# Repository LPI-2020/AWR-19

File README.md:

# Analog Waiter Robot (AWR-19)

Developed in:
- Projeto Integrador - LPI I (2020)

Members:
- Bruno Miguel Vasconcelos da Silva, a88289
- Diogo Miguel Cunha Fernandes, a88262
- Duarte Miguel Novo Rodrigues, a88259
- Francisco Lopes Salgado, a88231 
- João Pedro Dias Miranda, a88237
- José Tomás Lima de Abreu, a88218

Directed by:
- Luís Barros

Short description (PT):
- O Analog Waiter Robot (AWR) é um robô seguidor de linha focado na assistência a pessoas em isolamento que não podem contactar com o mundo exterior. Basta colocar no seu suporte o que pretende fazer chegar ao paciente, colocá-lo sobre a linha, ligá-lo e este seguirá o percurso até ao destino.

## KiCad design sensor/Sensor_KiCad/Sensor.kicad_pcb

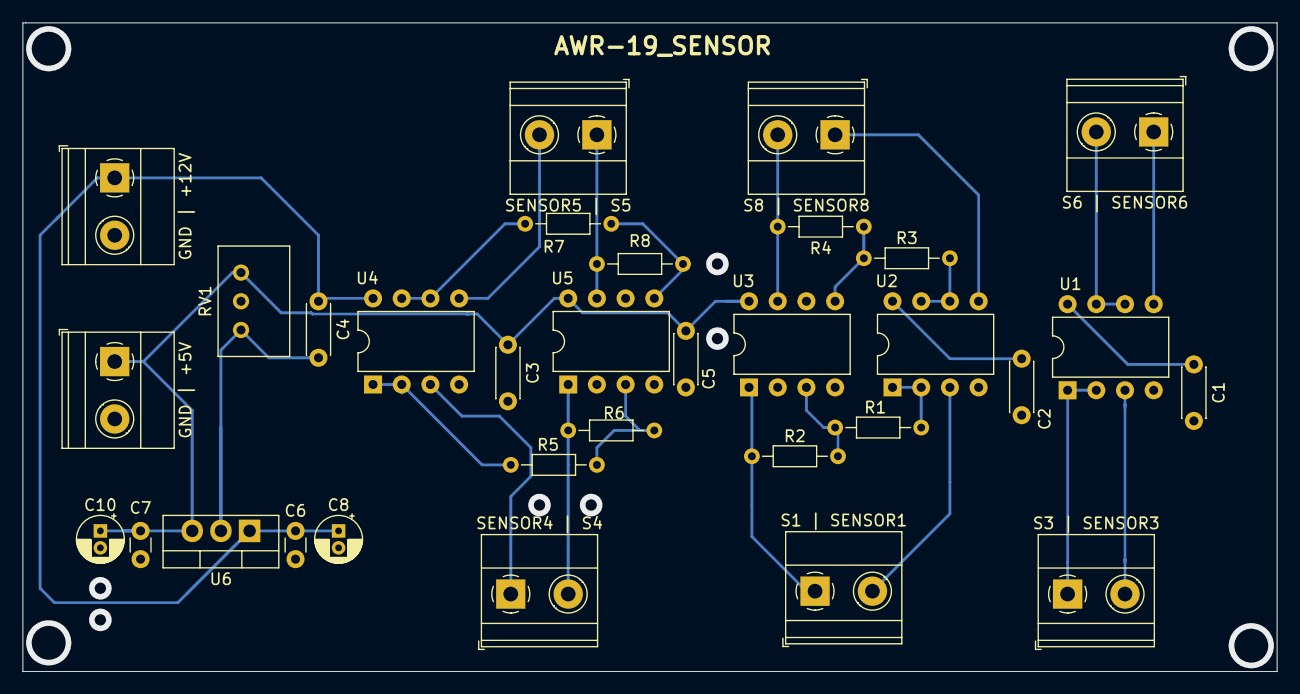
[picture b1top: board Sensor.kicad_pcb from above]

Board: 2 copper layers, 111.0 x 57.4 mm, 32 parts (0 on the bottom side), 24 nets.

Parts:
C1, C2, C3, C4, C5: C; C_Disc_D4.3mm_W1.9mm_P5.00mm
C6, C7: C; C_Disc_D3.0mm_W1.6mm_P2.50mm
C8, C10: CP_Small; CP_Radial_D4.0mm_P1.50mm
GND | +5V, GND | +12V: Conn_01x02_Female; TerminalBlock_Phoenix_MKDS-1,5-2-5.08_1x02_P5.08mm_Horizont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
R1, R3: 1k; R_Axial_DIN0204_L3.6mm_D1.6mm_P7.62mm_Horizontal
R2, R4: 10k; R_Axial_DIN0204_L3.6mm_D1.6mm_P7.62mm_Horizontal
R5, R6, R7, R8: R; R_Axial_DIN0204_L3.6mm_D1.6mm_P7.62mm_Horizontal
RV1: R_POT; Potentiometer_Bourns_3299W_Vertical
S1 | SENSOR1, S3 | SENSOR3, S6 | SENSOR6, S8 | SENSOR8: Conn_01x02_Female; TerminalBlock_Phoenix_MKDS-1,5-2-5.08_1x02_P5.08mm_Horizont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
SENSOR4 | S4, SENSOR5 | S5: Conn_01x02_Female; TerminalBlock_Phoenix_MKDS-1,5-2-5.08_1x02_P5.08mm_Horizont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
U1, U2, U3, U4, U5: LM358; DIP-8_W7.62mm
U6: LM7805_TO220; TO-220-3_Vertical

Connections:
+5V: C3.1, C5.1, C7.1, C10.1, GND | +5V.1, RV1.1, U3.8, U5.8, U6.3
+12V: C1.1, C2.1, C4.1, C6.1, C8.1, GND | +12V.1, U1.8, U2.8, U4.8, U6.1
GND: C1.2, C2.2, C3.2, C4.2, C5.2, C6.2, C7.2, C8.2, C10.2, GND | +5V.2, GND | +12V.2, RV1.3, U1.4, U2.4, U3.4, U4.4, U5.4, U6.2
IN_SENSOR1: S1 | SENSOR1.2, U2.3
IN_SENSOR3: S3 | SENSOR3.2, U1.3
IN_SENSOR4: SENSOR4 | S4.1, U4.3
IN_SENSOR5: SENSOR5 | S5.2, U4.5
IN_SENSOR6: S6 | SENSOR6.1, U1.5
IN_SENSOR8: S8 | SENSOR8.1, U2.5
unnamed: R1.1, U2.1, U2.2
unnamed: R1.2, R2.1, U3.3
unnamed: R3.1, U2.6, U2.7
unnamed: R3.2, R4.1, U3.5
unnamed: R5.1, U4.1, U4.2
unnamed: R5.2, R6.1, U5.3
unnamed: R7.1, U4.6, U4.7
unnamed: R7.2, R8.1, U5.5
OUT_SENSOR1: R2.2, S1 | SENSOR1.1, U3.1
OUT_SENSOR3: S3 | SENSOR3.1, U1.1, U1.2
OUT_SENSOR4: R6.2, SENSOR4 | S4.2, U5.1
OUT_SENSOR5: R8.2, SENSOR5 | S5.1, U5.7
OUT_SENSOR6: S6 | SENSOR6.2, U1.6, U1.7
OUT_SENSOR8: R4.2, S8 | SENSOR8.2, U3.7
VREF: RV1.2, U3.2, U3.6, U5.2, U5.6

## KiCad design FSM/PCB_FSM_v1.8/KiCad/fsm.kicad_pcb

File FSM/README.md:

# PI-LPI_I/FSM

**_Version_ currently in use: v1.8**

Resources - Holds various materials that helped or will help implement features.

v1 - Robot makes 180 degree turn when arriving at the end of the line and then stops.
     After that, whenever the user wants to send back the robot, a button can be pressed to begin movement.

v2 - Robot stops at the end of the line. After that, whenever the user wants to send back the robot,
     a button can be pressed to begin movement in the opposite direction that he came.

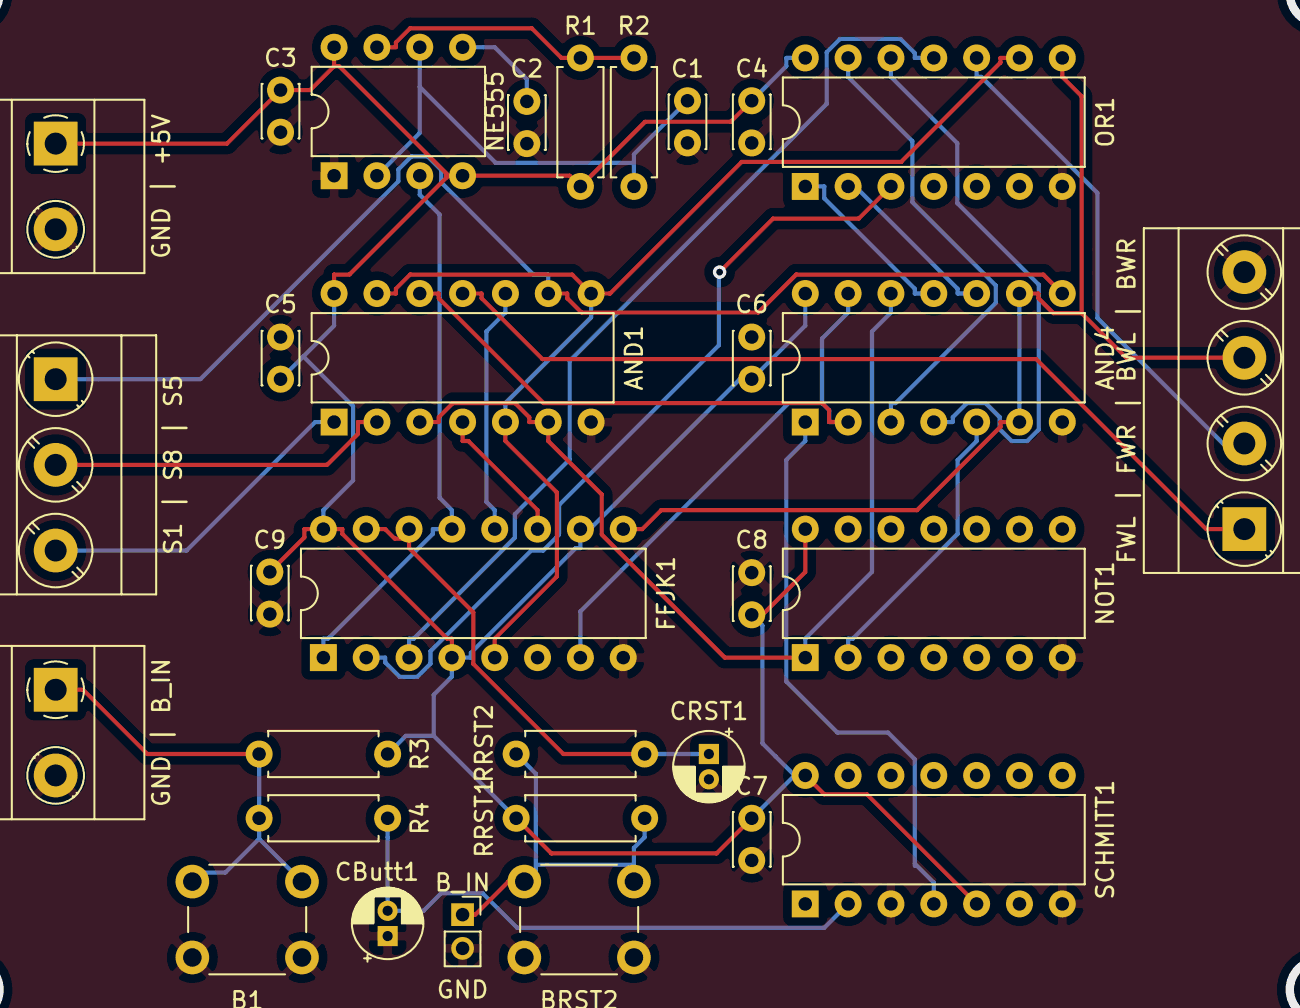
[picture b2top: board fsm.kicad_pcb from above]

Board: 2 copper layers, 31 parts (0 on the bottom side), 29 nets.

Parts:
AND1, AND4: 4081; DIP-14_W7.62mm
B1: SW_Push; SW_PUSH_6mm_H7.3mm
BRST2: SW_Push; SW_PUSH_6mm_H7.3mm
C1: 4,7u; C_Disc_D3.0mm_W2.0mm_P2.50mm
C2, C3, C4, C5, C6, C7, C8, C9: 10n; C_Disc_D3.0mm_W2.0mm_P2.50mm
CButt1: 10n; CP_Radial_D4.0mm_P1.50mm
CRST1: 10n; CP_Radial_D4.0mm_P1.50mm
FFJK1: 74LS76; DIP-16_W7.62mm
FWL | FWR | BWL | BWR: Conn_01x04_Female; TerminalBlock_Phoenix_MKDS-3-4-5.08_1x04_P5.08mm_Horizontal
GND: Conn_01x02_Female; PinSocket_1x02_P2.00mm_Vertical
GND | +5V: Conn_01x02_Female; TerminalBlock_Phoenix_MKDS-1,5-2-5.08_1x02_P5.08mm_Horizont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
GND | B_IN: Conn_01x02_Female; TerminalBlock_Phoenix_MKDS-1,5-2-5.08_1x02_P5.08mm_Horizont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
NE555: NE555P; DIP-8_W7.62mm
NOT1: 74LS04; DIP-14_W7.62mm
OR1: 4071; DIP-14_W7.62mm
R1: 6,2k; R_Axial_DIN0207_L6.3mm_D2.5mm_P7.62mm_Horizontal
R2: 150k; R_Axial_DIN0207_L6.3mm_D2.5mm_P7.62mm_Horizontal
R3: 10k; R_Axial_DIN0207_L6.3mm_D2.5mm_P7.62mm_Horizontal
R4: 1k; R_Axial_DIN0207_L6.3mm_D2.5mm_P7.62mm_Horizontal
RRST1, RRST2: 100k; R_Axial_DIN0207_L6.3mm_D2.5mm_P7.62mm_Horizontal
S1 | S8 | S5: Conn_01x03_Female; TerminalBlock_Phoenix_MKDS-3-3-5.08_1x03_P5.08mm_Horizontal
SCHMITT1: SN74LVC1G14DRL; DIP-14_W7.62mm

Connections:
+5V: AND1.14, AND4.14, C3.1, C4.1, C5.1, C6.1, C7.1, C8.1, C9.1, FFJK1.4, FFJK1.10, FFJK1.16, GND | +5V.1, NE555.4, NE555.8, NOT1.14, OR1.14, R1.1, R3.1, RRST1.1, SCHMITT1.5, SCHMITT1.14
B: AND4.1, SCHMITT1.4
B0: AND1.5, AND1.8, AND1.13, FFJK1.5, OR1.9
B1': AND1.12, AND4.2, AND4.13, FFJK1.7
BWL: AND4.6, AND4.9, FFJK1.9, FWL | FWR | BWL | BWR.3, OR1.8
B_IN: B1.2, GND | B_IN.1, R3.2, R4.1
CLK: FFJK1.1, FFJK1.13, NE555.3
FWL: AND1.11, FWL | FWR | BWL | BWR.1
FWR: FWL | FWR | BWL | BWR.2, OR1.10
GND: AND1.7, AND4.7, B1.1, BRST2.1, C1.2, C2.1, C3.2, C4.2, C5.2, C6.2, C7.2, C8.2, C9.2, CButt1.1, CRST1.2, FFJK1.8, FWL | FWR | BWL | BWR.4, GND.2, GND | +5V.2, GND | B_IN.2, NE555.1, NOT1.7, OR1.7, SCHMITT1.3, SCHMITT1.7
unnamed: AND1.3, AND1.6, AND4.12, NOT1.1
unnamed: AND1.4, FFJK1.11
unnamed: AND1.10, FFJK1.12
unnamed: AND4.3, OR1.13
unnamed: AND4.4, OR1.12
unnamed: AND4.5, NOT1.2
unnamed: AND4.10, OR1.2
unnamed: AND4.11, OR1.1
unnamed: BRST2.2, GND.1, RRST1.2, RRST2.1
unnamed: C1.1, NE555.2, NE555.6, R2.2
unnamed: C2.2, NE555.5
unnamed: CButt1.2, R4.2, SCHMITT1.2
unnamed: FFJK1.2, OR1.3
unnamed: FFJK1.3, OR1.11
unnamed: NE555.7, R1.2, R2.1
RESET: CRST1.1, FFJK1.14, FFJK1.15, RRST2.2
S1: AND1.1, S1 | S8 | S5.3
S5: AND1.9, AND4.8, S1 | S8 | S5.1
S8: AND1.2, S1 | S8 | S5.2

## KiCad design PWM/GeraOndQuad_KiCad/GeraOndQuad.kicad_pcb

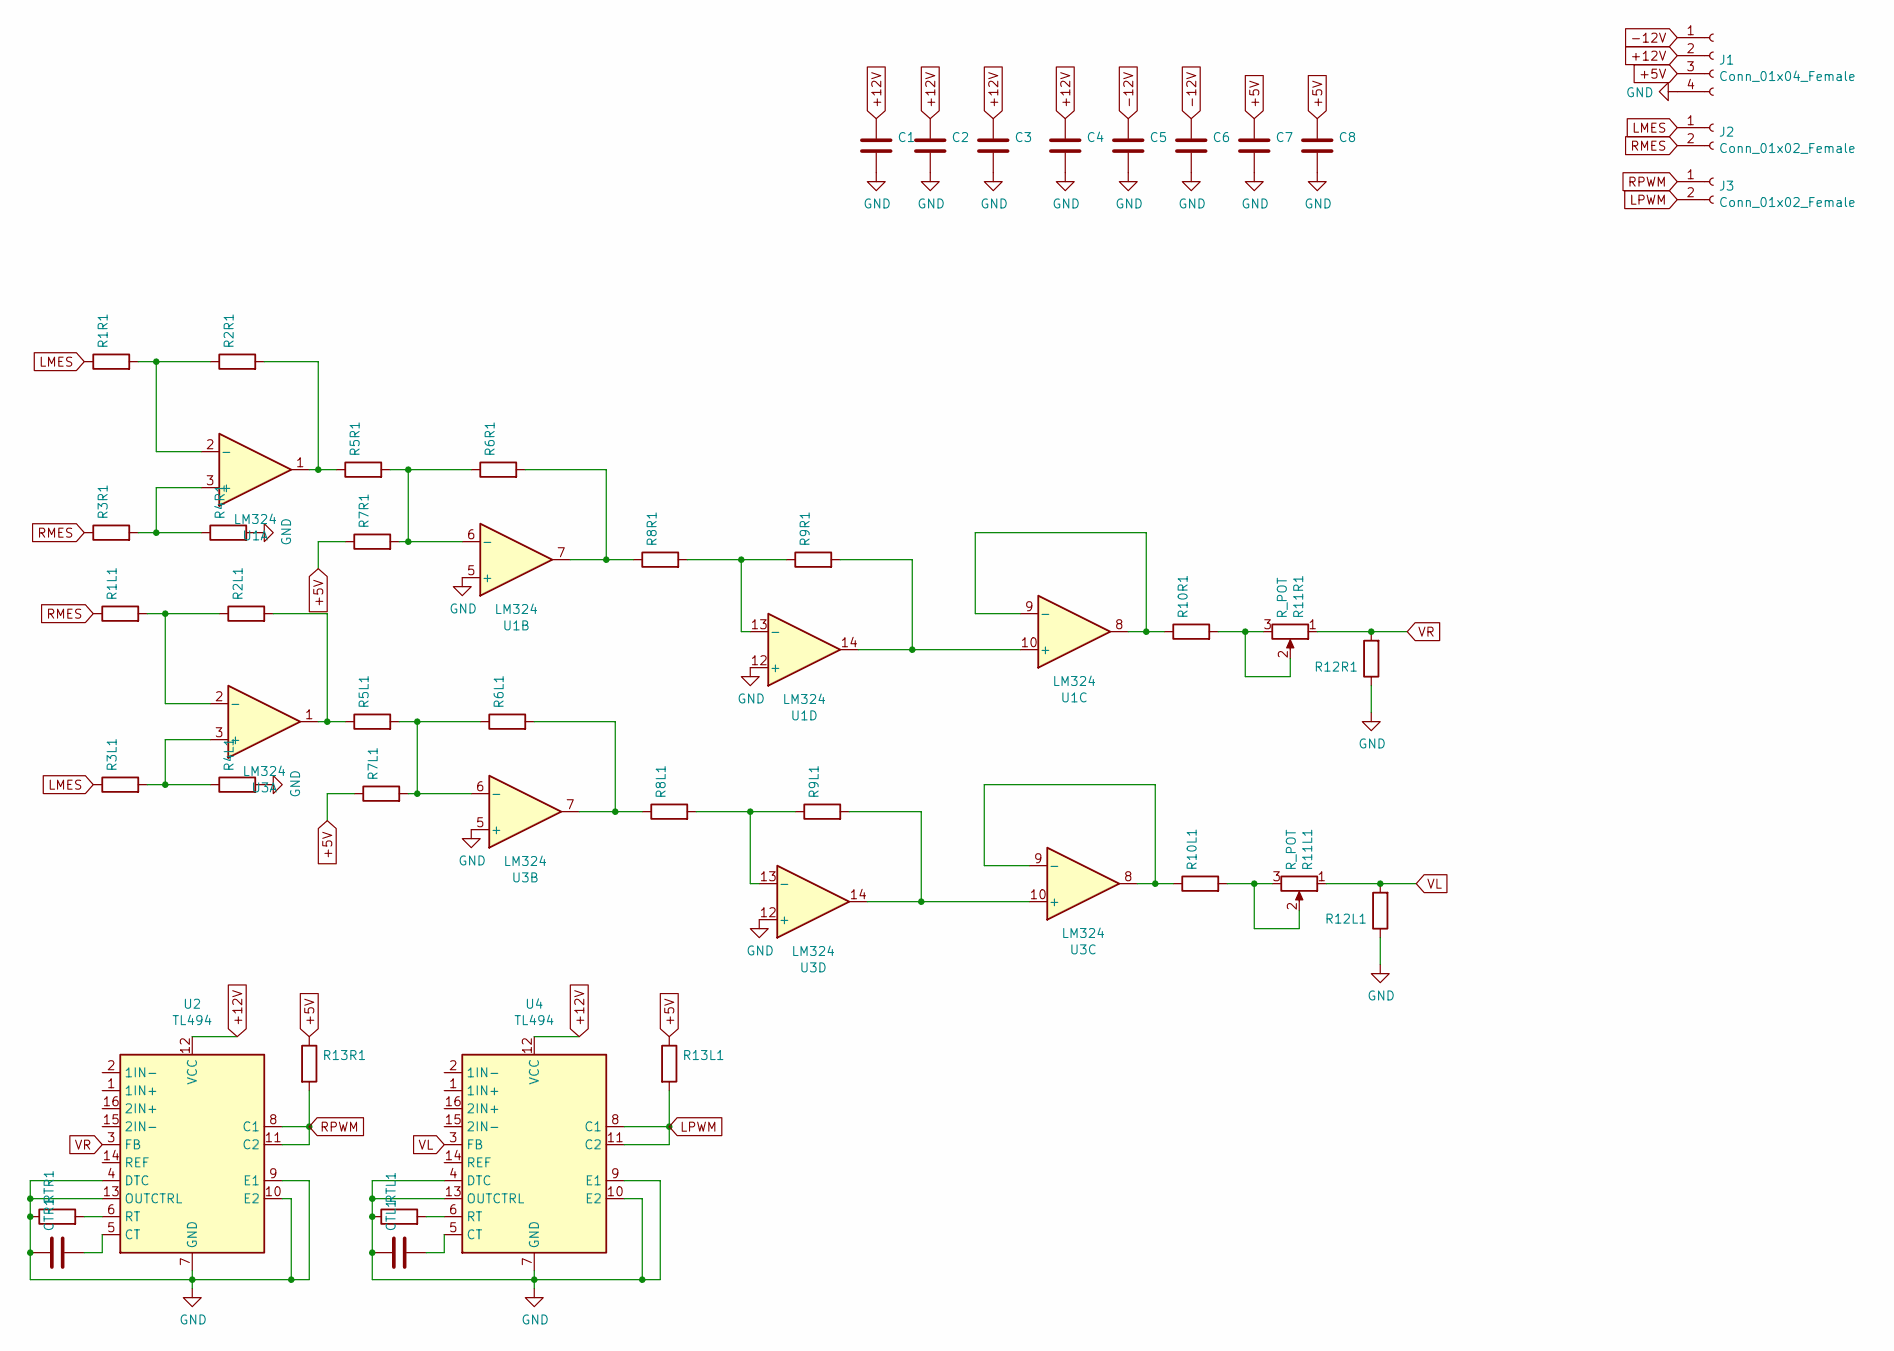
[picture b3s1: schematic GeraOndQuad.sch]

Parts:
C1, C2, C3, C4, C5, C6, C7, C8: C; C_Disc_D3.0mm_W1.6mm_P2.50mm
CTL1: C; C_Disc_D3.0mm_W1.6mm_P2.50mm
CTR1: C; C_Disc_D3.0mm_W1.6mm_P2.50mm
J1: Conn_01x04_Female; TerminalBlock_Phoenix_MKDS-1,5-4_1x04_P5.00mm_Horizontal
J2, J3: Conn_01x02_Female; TerminalBlock_Phoenix_MKDS-1,5-2-5.08_1x02_P5.08mm_Horizont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
R1L1, R1R1, R2L1, R2R1, R3L1, R3R1, R4L1, R4R1, R5L1, R5R1, R6L1, R6R1, R7L1, R7R1, R8L1, R8R1, R9L1, R9R1, R10L1, R10R1, R12L1, R12R1, R13L1, R13R1: R; R_Axial_DIN0204_L3.6mm_D1.6mm_P7.62mm_Horizontal
R11L1, R11R1: R_POT; Potentiometer_Bourns_3299W_Vertical
RTL1: R; R_Axial_DIN0204_L3.6mm_D1.6mm_P7.62mm_Horizontal
RTR1: R; R_Axial_DIN0204_L3.6mm_D1.6mm_P7.62mm_Horizontal
U1, U3: LM324; DIP-14_W7.62mm
U2, U4: TL494; DIP-16_W10.16mm

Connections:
+5V: C7.1, C8.1, J1.3, R7L1.1, R7R1.1, R13L1.1, R13R1.1; also elsewhere on the board
+12V: C1.1, C2.1, C3.1, C4.1, J1.2, U1.4 (V+), U2.12 (VCC), U3.4 (V+), U4.12 (VCC); also elsewhere on the board
-12V: C5.1, C6.1, J1.1, U1.11 (V-), U3.11 (V-); also elsewhere on the board
GND: C1.2, C2.2, C3.2, C4.2, C5.2, C6.2, C7.2, C8.2, CTL1.1, CTR1.1, J1.4, R4L1.2, R4R1.2, R12L1.1, R12R1.1, RTL1.1, RTR1.1, U1.5 (+), U1.12 (+), U2.4 (DTC), U2.7 (GND), U2.9 (E1), U2.10 (E2), U2.13 (OUTCTRL), U3.5 (+), U3.12 (+), U4.4 (DTC), U4.7 (GND), U4.9 (E1), U4.10 (E2), U4.13 (OUTCTRL); also elsewhere on the board
LMES: J2.1, R1R1.1, R3L1.1; also elsewhere on the board
LPWM: J3.2, R13L1.2, U4.8 (C1), U4.11 (C2); also elsewhere on the board
unnamed: CTL1.2, U4.5 (CT)
unnamed: CTR1.2, U2.5 (CT)
unnamed: R1L1.2, R2L1.1, U3.2 (-)
unnamed: R1R1.2, R2R1.1, U1.2 (-)
unnamed: R2L1.2, R5L1.1, U3.1
unnamed: R2R1.2, R5R1.1, U1.1
unnamed: R3L1.2, R4L1.1, U3.3 (+)
unnamed: R3R1.2, R4R1.1, U1.3 (+)
unnamed: R5L1.2, R6L1.1, R7L1.2, U3.6 (-)
unnamed: R5R1.2, R6R1.1, R7R1.2, U1.6 (-)
unnamed: R6L1.2, R8L1.1, U3.7
unnamed: R6R1.2, R8R1.1, U1.7
unnamed: R8L1.2, R9L1.1, U3.13 (-)
unnamed: R8R1.2, R9R1.1, U1.13 (-)
unnamed: R9L1.2, U3.10 (+), U3.14
unnamed: R9R1.2, U1.10 (+), U1.14
unnamed: R10L1.1, U3.8, U3.9 (-)
unnamed: R10L1.2, R11L1.2, R11L1.3
unnamed: R10R1.1, U1.8, U1.9 (-)
unnamed: R10R1.2, R11R1.2, R11R1.3
unnamed: RTL1.2, U4.6 (RT)
unnamed: RTR1.2, U2.6 (RT)
RMES: J2.2, R1L1.1, R3R1.1; also elsewhere on the board
RPWM: J3.1, R13R1.2, U2.8 (C1), U2.11 (C2); also elsewhere on the board
VL: R11L1.1, R12L1.2, U4.3 (FB)
VR: R11R1.1, R12R1.2, U2.3 (FB)

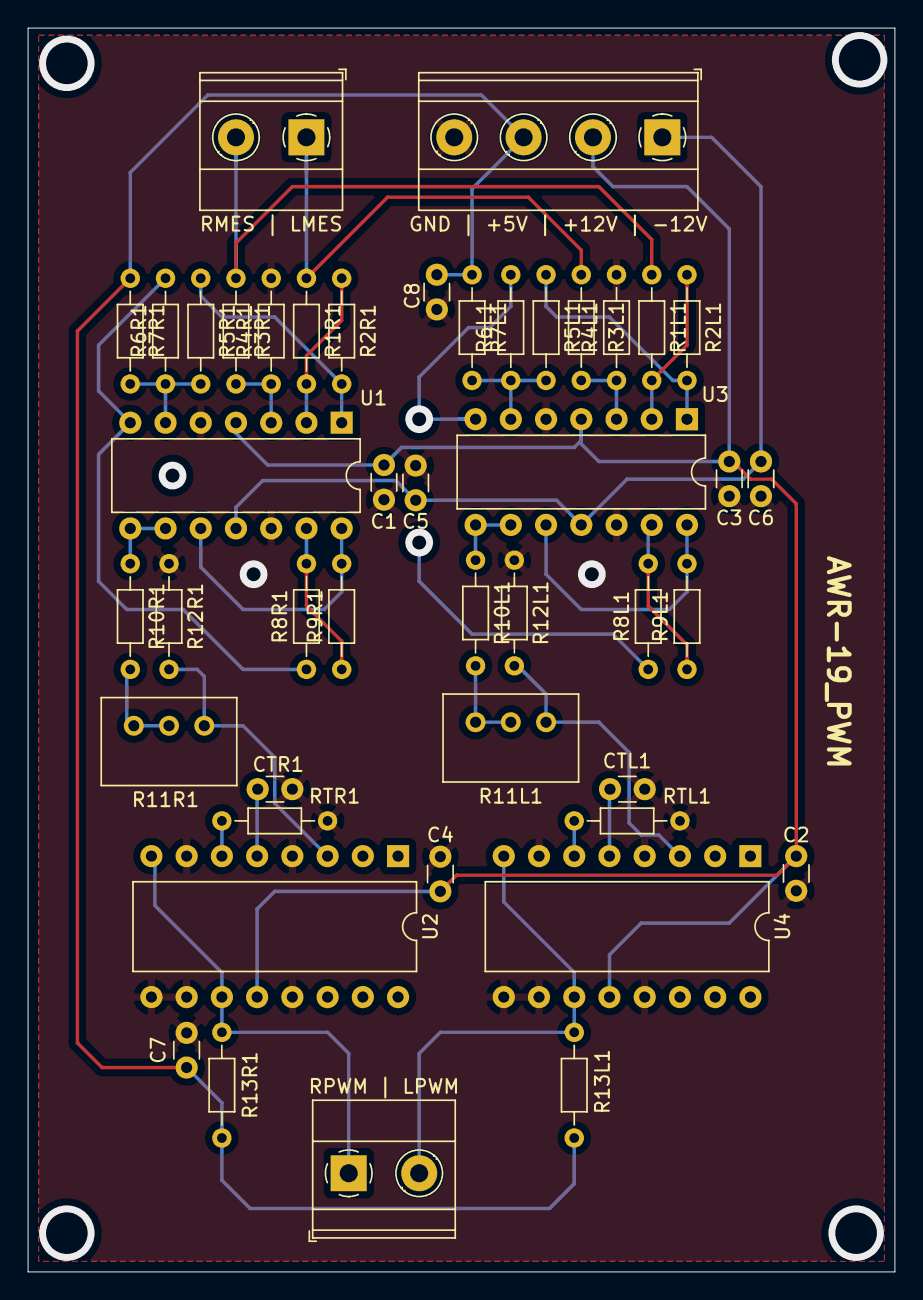
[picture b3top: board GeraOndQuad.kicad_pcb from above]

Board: 2 copper layers, 62.5 x 89.7 mm, 45 parts (0 on the bottom side), 32 nets.

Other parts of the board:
GND | +5V | +12V | -12V: Conn_01x04_Female; TerminalBlock_Phoenix_MKDS-1,5-4_1x04_P5.00mm_Horizontal
RMES | LMES: Conn_01x02_Female; TerminalBlock_Phoenix_MKDS-1,5-2-5.08_1x02_P5.08mm_Horizont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
RPWM | LPWM: Conn_01x02_Female; TerminalBlock_Phoenix_MKDS-1,5-2-5.08_1x02_P5.08mm_Horizont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

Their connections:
+5V: GND | +5V | +12V | -12V.3; also elsewhere on the board
+12V: GND | +5V | +12V | -12V.2; also elsewhere on the board
-12V: GND | +5V | +12V | -12V.1; also elsewhere on the board
GND: GND | +5V | +12V | -12V.4; also elsewhere on the board
LMES: RMES | LMES.1; also elsewhere on the board
LPWM: RPWM | LPWM.2; also elsewhere on the board
RMES: RMES | LMES.2; also elsewhere on the board
RPWM: RPWM | LPWM.1; also elsewhere on the board

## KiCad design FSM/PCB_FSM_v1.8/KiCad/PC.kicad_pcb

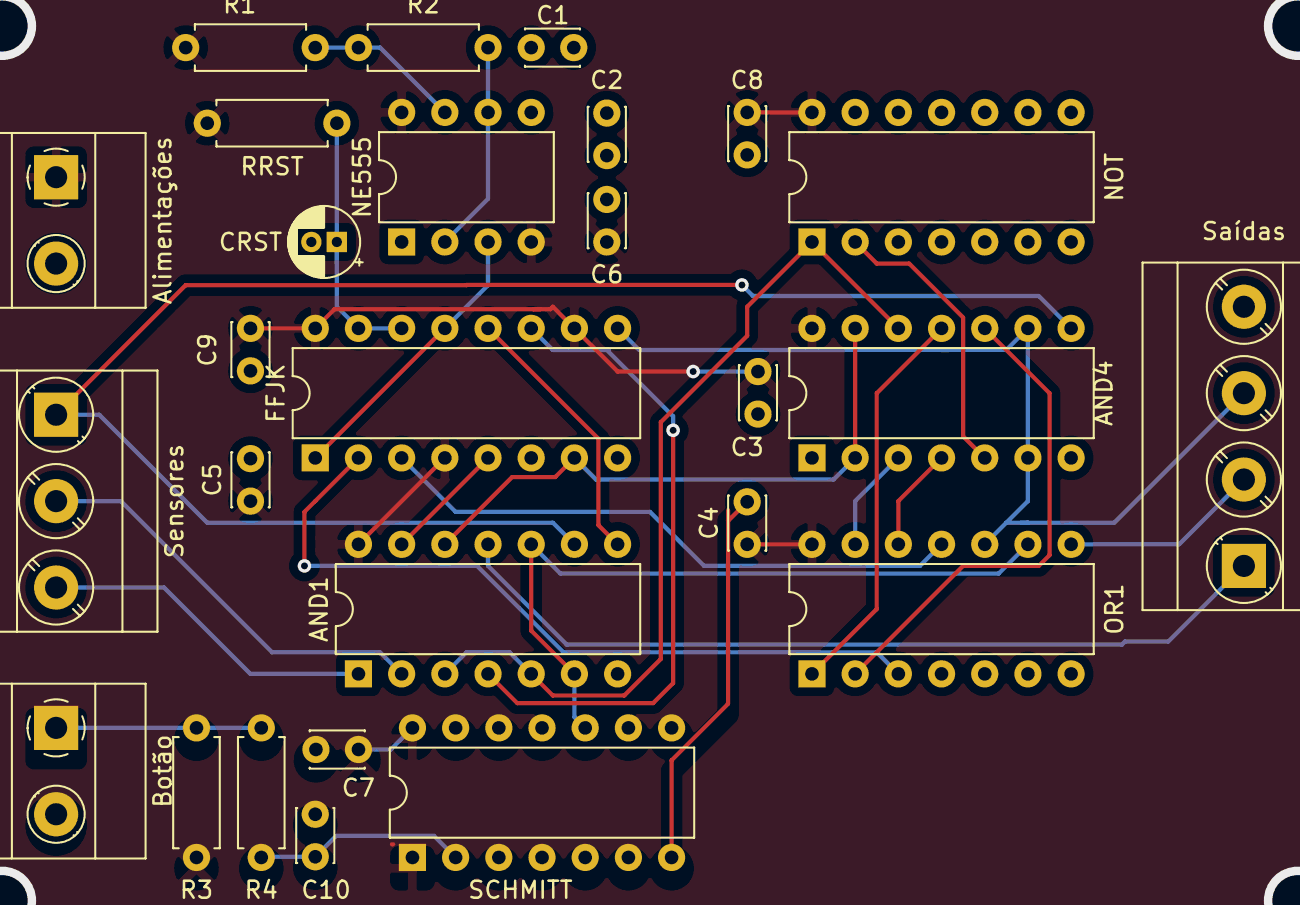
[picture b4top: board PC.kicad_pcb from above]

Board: 2 copper layers, 27 parts (0 on the bottom side), 27 nets.

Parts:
AND1, AND4: 4081; DIP-14_W7.62mm
Alimentações: Conn_01x02_Female; TerminalBlock_Phoenix_MKDS-1,5-2-5.08_1x02_P5.08mm_Horizont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
Botão: Conn_01x02_Female; TerminalBlock_Phoenix_MKDS-1,5-2-5.08_1x02_P5.08mm_Horizont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
C1: 4,7u; C_Disc_D3.0mm_W2.0mm_P2.50mm
C2, C3, C4, C5, C6, C7, C8, C9, C10: 10n; C_Disc_D3.0mm_W2.0mm_P2.50mm
CRST: 10n; CP_Radial_D4.0mm_P1.50mm
FFJK: 74LS76; DIP-16_W7.62mm
NE555: NE555P; DIP-8_W7.62mm
NOT: 74LS04; DIP-14_W7.62mm
OR1: 4071; DIP-14_W7.62mm
R1, R3, R4: 6,2k; R_Axial_DIN0207_L6.3mm_D2.5mm_P7.62mm_Horizontal
R2: 150k; R_Axial_DIN0207_L6.3mm_D2.5mm_P7.62mm_Horizontal
RRST: 100k; R_Axial_DIN0207_L6.3mm_D2.5mm_P7.62mm_Horizontal
SCHMITT: SN74LVC1G14DRL; DIP-14_W7.62mm
Saídas: Conn_01x04_Female; TerminalBlock_Phoenix_MKDS-3-4-5.08_1x04_P5.08mm_Horizontal
Sensores: Conn_01x03_Female; TerminalBlock_Phoenix_MKDS-3-3-5.08_1x03_P5.08mm_Horizontal

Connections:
+5V: AND1.14, AND4.14, Alimentações.1, C3.1, C4.1, C5.1, C6.1, C7.1, C8.1, C9.1, FFJK.4, FFJK.10, FFJK.16, NE555.4, NE555.8, NOT.14, OR1.14, R1.1, R3.1, RRST.1, SCHMITT.1, SCHMITT.14
B0: AND1.6, AND1.10, AND1.13, FFJK.5, OR1.9, SCHMITT.10
B1': AND1.12, AND4.2, AND4.13, FFJK.7
BWL: AND4.6, AND4.9, FFJK.9, OR1.10, Saídas.3
B_IN: Botão.1, R3.2, R4.1
CLK: FFJK.1, FFJK.13, NE555.3
FWL: AND1.11, Saídas.1
FWR: OR1.8, Saídas.2
GND: AND1.7, AND4.7, Alimentações.2, Botão.2, C1.2, C2.1, C3.2, C4.2, C5.2, C6.2, C7.2, C8.2, C9.2, C10.1, CRST.2, FFJK.8, NE555.1, NOT.7, OR1.7, SCHMITT.7, Saídas.4
unnamed: AND1.3, AND1.5, AND4.12, NOT.1
unnamed: AND1.4, FFJK.11
unnamed: AND1.8, FFJK.12
unnamed: AND4.3, OR1.13
unnamed: AND4.4, OR1.12
unnamed: AND4.5, NOT.2
unnamed: AND4.10, OR1.2
unnamed: AND4.11, OR1.1
unnamed: C1.1, NE555.2, NE555.6, R2.2
unnamed: C2.2, NE555.5
unnamed: C10.2, R4.2, SCHMITT.2
unnamed: FFJK.2, OR1.3
unnamed: FFJK.3, OR1.11
unnamed: NE555.7, R1.2, R2.1
RESET: CRST.1, FFJK.14, FFJK.15, RRST.2
S1: AND1.1, Sensores.3
S5: AND1.9, AND4.8, Sensores.1
S8: AND1.2, Sensores.2

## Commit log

2020-12-19 Added old updates.
2020-12-22 Added resources, updated ne555-simulations.
2020-12-22 Moved files from /fsm/resources to /documentation
2020-12-23 2.3 correction and 2.4
2020-12-24 add components and prices
2020-12-28 Removed non essential files
2020-12-29 Added templates for PADs projects.
2020-12-29 Added some notes - TODO.txt!
2020-12-30 Added push button pinout to /resources
2020-12-30 Added more notes to TODO.txt
2021-01-02 Adding some connections, in and out jumpers. Please, checkout TODO.txt.
2021-01-07 FSM/PCB_FSM/fsm_design_reduced is not working. Multisim bug i think
2021-01-20 Version 2.5 currently working
2021-01-20 Starting pcb_fsm
2021-01-21 Working on pcb_fsm
2021-01-23 PWM generator without a reference
2021-01-23 correction of some error
2021-01-23 sensor circuits
2021-01-24 add datasheet
2021-01-24 added excel with tests
2021-01-24 last version pads layout (with errors)
2021-01-24 continuation
2021-01-24 maybe it needs +12V on top
2021-01-25 Working on fsm_pcb
2021-01-25 PCB almost finished - no errors
2021-01-25 Added fsm_v1.8
2021-01-25 PCB v1.8
2021-01-25 PCB first changes
2021-01-25 sensor and pwm pcb finished
2021-01-25 holy shit
2021-01-25 added voltagegenerator
2021-01-25 added LM7805 datasheet
2021-01-26 Relatorio added
2021-01-26 Sensor PCB finished
2021-01-26 decoupling capacitors
2021-01-26 added voltage generator PCB
2021-01-26 FSM Relatorio Final
2021-01-26 minor errors corrected
2021-01-26 add voltageGenerator to PCB
2021-01-26 Relatório FSM
2021-01-26 PDF and DWG files for robot diagrams
2021-01-26 Fixed .sch errors
2021-01-26 Correct fsm diagram added
2021-01-27 GerOndQuad updated
2021-01-27 Sensor PCB corrected
2021-01-27 Struct
2021-01-27 Alterações no relatorio
2021-01-27 Relatório
2021-01-27 coadded comments in the simulation
2021-01-27 Sensor and GeraOndQuad finished
2021-01-27 PCB done
2021-01-27 Tina edited
2021-01-27 Added final fsm_pcb version
2021-01-27 Added tmp version of pcb_debounce
2021-01-27 Updated Mechanical Diagrams
    Almost complete, while viewing in pdf lines appear grey because they're too thin, this issue will get resolved later
2021-01-27 simulation edited
2021-01-27 iniciation
2021-01-27 Continuing Relatorio
2021-01-27 Added push-button logic & layout
2021-01-27 PTA Q PRREU
2021-01-28 Added fsm_LB
2021-01-28 added image
2021-01-28 bibliography
2021-01-28 added relatorio_revisao
2021-01-28 added Kickad sensor
2021-01-28 Added final version fsm_LB
2021-01-28 print simultions
2021-01-28 Diagram Updated and 3D Model Started
    Do not open the pdf file with Adobe Acrobat Reader to take prints, use other pdf viewer (chrome works for me) where lines don't appear grey. STL file is a 3D file format.
2021-01-28 Corrected a small organization mistake
2021-01-28 motor control simulation completed
2021-01-28 update simulation
2021-01-28 added KiCad files
2021-01-29 KiCad final
2021-01-29 reorder
2021-01-29 corrections
2021-01-29 labels
2021-01-29 finished
2021-01-29 labels corrections
2021-01-29 Pega bruno
2021-01-29 Kicad projects finished
2021-01-29 Added fsm_LB_v1 & v2
2021-01-29 Renamed fsm_LB/
2021-01-29 corrected kiCad errors
2021-01-29 KiCad over
2021-01-29 fsm design correction
2021-01-29 Kicad GeraOndQuad update
2021-01-29 simulations and PCB
2021-01-29 Renamed some files and deleted trash
2021-01-29 Changed version in use
2021-01-30 GeraOndQuad Kicad name update
2021-01-30 update colors PADS and name in Kicad
2021-01-30 update sensor pads and Kicad
2021-01-30 PCB prints finished
2021-01-30 Relatório final review
2021-01-31 components list and robot design
2021-02-01 resitor value
2021-02-01 alteration in 3D view
2021-02-01 Added missing dimensions and corrected some errors
2021-02-01 Improved pdf output
2021-02-01 edit resistor value
2021-02-01 state machine PCB
2021-02-01 relatorio
2021-02-01 update index
2021-02-01 PCB 3D
2021-02-01 added pcb prints
2021-02-01 Renamed some files
2021-02-01 Continuation of Relatorio
2021-02-02 Added logicalParts datasheets
2021-02-02 Added components
2021-02-02 melhorias ao circuito nao concluidas
2021-02-03 Changed OR type on sch
2021-02-03 cap 7, cap 6
2021-02-03 Relatorio final alterations
2021-02-06 formataçoes
2021-02-06 multisim -> edit output names
2021-02-07 original file
2021-02-07 relatorio com formatacoes corretas (espero)
2021-02-07 debounce: deleting R3
2021-02-07 relatorio fsm added
2021-02-08 Cap 2.4 end; improving 4.
2021-02-08 Cap 2.4 end; improving 4.4
2021-02-08 cap 2.2 2.3 2.4
2021-02-08 RelatorioFinal_FSM done
2021-02-08 refresh images
2021-02-08 juntar as duas partes - inicio
2021-02-08 Cap 6 done
2021-02-08 tudo junto. Falta o que e para ser feito em conjunto
2021-02-08 conclusao done and cap 7
2021-02-08 fotos robo
2021-02-08 edited simulations (output/input names)
2021-02-08 less size images
2021-02-08 add simulation print
2021-02-09 continue
2021-02-09 debounce images
2021-02-09 Working on
2021-02-10 add apresentation, pictures and movies used
2021-02-10 RelatórioFinal done
2021-02-10 Revised
2021-02-11 add apresentation
2021-02-11 Relatorio done
2021-02-11 ACABOU
2021-02-11 apresentacao feita: - divisao de tarefas
2021-02-12 Added ppt
2021-02-26 Final commit
